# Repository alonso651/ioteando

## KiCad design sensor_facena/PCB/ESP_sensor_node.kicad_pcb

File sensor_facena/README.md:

Sensor de Humedad, Temperatura y Luz
========================================
Febrero de 2020 

Comandos que acepta
------------------------------

1. {"comando":"chipId}
2. {"comando":"loopTime", "valor":5000}

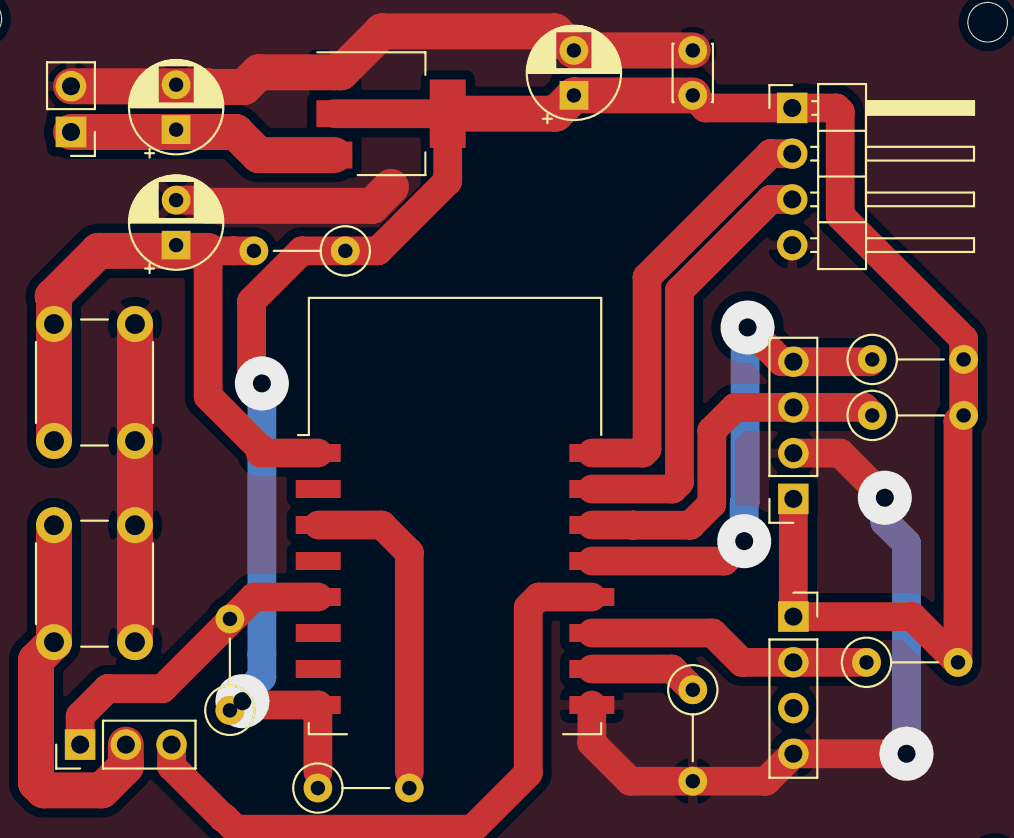
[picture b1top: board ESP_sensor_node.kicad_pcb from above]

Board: 2 copper layers, 20 parts (0 on the bottom side), 14 nets.

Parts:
C1, C3, C4: 100nF; CP_Radial_D5.0mm_P2.50mm
C2: 100 nF; C_Disc_D3.0mm_W2.0mm_P2.50mm
J1: BH1750; PinSocket_1x04_P2.54mm_Vertical
J2: DHT11; PinSocket_1x04_P2.54mm_Vertical
J3: SERIAL; PinHeader_1x04_P2.54mm_Horizontal
J4: FLASH; PinHeader_1x03_P2.54mm_Vertical
J5: ALIMENTACIÓN; PinHeader_1x02_P2.54mm_Vertical
R1, R2, R3, R4, R5, R6, R7: 10K; R_Axial_DIN0207_L6.3mm_D2.5mm_P5.08mm_Vertical
SW1: FLASH; SW_PUSH_6mm
SW2: RESET; SW_PUSH_6mm
U1: ESP-12E
U2: AMS1117-3.3; SOT-223-3_TabPin2

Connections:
/3V3: C2.1, C3.1, J1.1, J2.1, J3.1, R1.1, R2.1, R3.2, R4.2, R5.2, R7.1, U1.8, U2.2
/5V: C4.1, J5.1, U2.3
/DHT_DATA: J2.2, R3.1, U1.17
/FACTORY_RST: J4.1, R7.2, U1.5
/GND: C1.2, C2.2, C3.2, C4.2, J1.2, J2.4, J3.4, J5.2, R6.2, SW1.1, SW2.1, U1.15, U2.1
/GPIO0: J4.3, U1.18
/INPUT_BUTTON: J4.2, SW1.2
/RST: C1.1, R1.2, SW2.2, U1.1
/RX: J3.3, U1.21
/SCL: J1.4, R5.1, U1.19
/SDA: J1.3, R4.1, U1.20
/TX: J3.2, U1.22
unnamed: R2.2, U1.3
unnamed: R6.1, U1.16

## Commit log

2019-09-15 sensor facena
    Sensor de temperatura, humedad e iluminación
2019-09-15 libraries
2019-09-15 version 1
2019-09-29 version 1.0
    reset factory por software
